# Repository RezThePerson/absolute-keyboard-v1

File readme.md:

# Absolute Keyboard v1

|  |  |
| --------------------------------------------------------------------------------------------------------------- | ------------------------------------------------------------------------------------------------------------------ |
|  |                                        |
|                                     |                                        |

A simple keeb with

- 65% layout (68 keey)
- rp2040 chip (aka embeeded custom board)
- neopixle for each switch
- hotspawp support
- minmilistic case
- qmk firmware

### Credits

guides:

- [Macondo's build a devboard](https://macondo.hackclub.com/docs/build-a-devboard)
- [Hackpad](https://hackpad.hackclub.com/guide)
- [Hackpad Advance Guide](https://hackpad-v2-backup.pages.dev/advancedguide) (only on backup page as of building this project)

other keebs i took inspiration from:

- [teds-kb-100](https://github.com/DovydasTEDS/teds-kb-100)
- [keeb-v2](https://github.com/Anayjain1129/keeb-v2)
- [FluxKeeb](https://github.com/Flux3tor/FluxKeeb)

kicad tools:

- [Keyboard footprints placer](https://github.com/adamws/kicad-kbplacer) plugin
- [MX_V2](https://github.com/ai03-2725/MX_V2) lib
- [marbast](https://github.com/ebastler/marbastlib) lib

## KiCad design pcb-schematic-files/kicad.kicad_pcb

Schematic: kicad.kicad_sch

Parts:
C1, C2, C3, C4, C5, C6, C7, C8, C10, C11, C17: 0.1uF; C_0402_1005Metric; LCSC C1525
C9, C12: 1uF; C_0402_1005Metric; LCSC C52923
C13, C14: 10uF; C_0603_1608Metric; LCSC 0603
C15, C16: 33pF; C_0402_1005Metric; LCSC C1562
C18: 100pF; C_0402_1005Metric; LCSC C1546
D1, D2, D3, D4, D5, D6, D7, D8, D9, D10, D11, D12, D13, D14, D15, D16, D17, D18, D19, D20, D21, D22, D23, D24, D25, D26, D27, D28, D29, D30, D31, D32, D33, D34, D35, D36, D37, D38, D39, D40, D41, D42, D43, D44, D45, D46, D47, D48, D49, D50, D51, D52, D53, D54, D55, D56, D57, D58, D59, D60, D61, D62, D63, D64, D65, D66, D67, D68: D; D_DO-35_SOD27_P7.62mm_Horizontal; LCSC 1N4148
J1: USB_C_Receptacle_USB2.0_14P; USB_C_Receptacle_HRO_TYPE-C-31-M-12; LCSC C165948
LED1, LED2, LED3, LED4, LED5, LED6, LED7, LED8, LED9, LED10, LED11, LED12, LED13, LED14, LED15, LED16, LED17, LED18, LED19, LED20, LED21, LED22, LED23, LED24, LED25, LED26, LED27, LED28, LED29, LED30, LED31, LED32, LED33, LED34, LED35, LED36, LED37, LED38, LED39, LED40, LED41, LED42, LED43, LED44, LED45, LED46, LED47, LED48, LED49, LED50, LED51, LED52, LED53, LED54, LED55, LED56, LED57, LED58, LED59, LED60, LED61, LED62, LED63, LED64, LED65, LED66, LED67, LED68: SK6812MINI-E; LED_6028R; LCSC C5149201
R1, R2: 5.1K; R_0402_1005Metric; LCSC C25905
R3, R4: 27; R_0402_1005Metric; LCSC C25100
R5, R6: 1K; R_0402_1005Metric; LCSC C11702
R7: 10K; R_0402_1005Metric; LCSC C25744
SW0: SW_Push; SW_Push_SPST_NO_Alps_SKRK; LCSC C115357
SW1, SW2, SW3, SW4, SW5, SW6, SW7, SW8, SW9, SW10, SW11, SW12, SW13, SW14, SW15, SW16, SW17, SW18, SW19, SW20, SW21, SW22, SW23, SW24, SW25, SW26, SW27, SW28, SW29, SW30, SW31, SW32, SW33, SW34, SW35, SW36, SW37, SW38, SW39, SW40, SW41, SW42, SW43, SW44, SW45, SW46, SW47, SW48, SW49, SW50, SW51, SW52, SW53, SW54, SW55, SW56, SW57, SW58, SW59, SW60, SW61, SW62, SW63, SW64, SW65, SW66, SW67, SW68: SW_Push; SW_MX_HS_CPG151101S11_1u; LCSC C49352235
U1: RP2040; QFN-56-1EP_7x7mm_P0.4mm_EP3.2x3.2mm; LCSC C2040
U2: NCP1117-3.3_SOT223; SOT-223-3_TabPin2; LCSC C6186
U3: W25Q128JVS; SOIC-8_5.3x5.3mm_P1.27mm; LCSC C97521
Y1: 12 MHz; Crystal_SMD_3225-4Pin_3.2x2.5mm; LCSC C9002

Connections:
+1V1: C10.1, C11.1, C12.1, U1.43 (ADC_AVDD), U1.48 (USB_VDD)
+3V3: C1.1, C2.1, C3.1, C4.1, C5.1, C6.1, C7.1, C8.1, C9.1, C14.1, C17.1, R7.2, U1.1 (IOVDD), U1.10 (IOVDD), U1.22 (IOVDD), U1.23 (DVDD), U1.33 (IOVDD), U1.42 (IOVDD), U1.44 (VREG_VIN), U1.45 (VREG_VOUT), U1.49 (IOVDD), U1.50 (DVDD), U2.2 (VO), U3.8 (VCC)
+5V: C13.1, C18.1, J1.A4 (VBUS), J1.A9 (VBUS), J1.B4 (VBUS), J1.B9 (VBUS), LED1.1 (VDD), LED2.1 (VDD), LED3.1 (VDD), LED4.1 (VDD), LED5.1 (VDD), LED6.1 (VDD), LED7.1 (VDD), LED8.1 (VDD), LED9.1 (VDD), LED10.1 (VDD), LED11.1 (VDD), LED12.1 (VDD), LED13.1 (VDD), LED14.1 (VDD), LED15.1 (VDD), LED16.1 (VDD), LED17.1 (VDD), LED18.1 (VDD), LED19.1 (VDD), LED20.1 (VDD), LED21.1 (VDD), LED22.1 (VDD), LED23.1 (VDD), LED24.1 (VDD), LED25.1 (VDD), LED26.1 (VDD), LED27.1 (VDD), LED28.1 (VDD), LED29.1 (VDD), LED30.1 (VDD), LED31.1 (VDD), LED32.1 (VDD), LED33.1 (VDD), LED34.1 (VDD), LED35.1 (VDD), LED36.1 (VDD), LED37.1 (VDD), LED38.1 (VDD), LED39.1 (VDD), LED40.1 (VDD), LED41.1 (VDD), LED42.1 (VDD), LED43.1 (VDD), LED44.1 (VDD), LED45.1 (VDD), LED46.1 (VDD), LED47.1 (VDD), LED48.1 (VDD), LED49.1 (VDD), LED50.1 (VDD), LED51.1 (VDD), LED52.1 (VDD), LED53.1 (VDD), LED54.1 (VDD), LED55.1 (VDD), LED56.1 (VDD), LED57.1 (VDD), LED58.1 (VDD), LED59.1 (VDD), LED60.1 (VDD), LED61.1 (VDD), LED62.1 (VDD), LED63.1 (VDD), LED64.1 (VDD), LED65.1 (VDD), LED66.1 (VDD), LED67.1 (VDD), LED68.1 (VDD), U2.3 (VI)
COL_1: SW1.1, SW16.1, SW31.1, SW45.1, SW59.1, U1.29 (GPIO18)
COL_2: SW2.1, SW17.1, SW32.1, SW46.1, SW60.1, U1.30 (GPIO19)
COL_3: SW3.1, SW18.1, SW33.1, SW47.1, SW61.1, U1.31 (GPIO20)
COL_4: SW4.1, SW19.1, SW34.1, SW48.1, SW62.1, U1.32 (GPIO21)
COL_5: SW5.1, SW20.1, SW35.1, SW49.1, U1.34 (GPIO22)
COL_6: SW6.1, SW21.1, SW36.1, SW50.1, U1.35 (GPIO23)
COL_7: SW7.1, SW22.1, SW37.1, SW51.1, U1.36 (GPIO24)
COL_8: SW8.1, SW23.1, SW38.1, SW52.1, U1.37 (GPIO25)
COL_9: SW9.1, SW24.1, SW39.1, SW53.1, SW63.1, U1.2 (GPIO0)
COL_10: SW10.1, SW25.1, SW40.1, SW54.1, SW64.1, U1.3 (GPIO1)
COL_11: SW11.1, SW26.1, SW41.1, SW55.1, SW65.1, U1.4 (GPIO2)
COL_12: SW12.1, SW27.1, SW42.1, SW56.1, SW66.1, U1.5 (GPIO3)
COL_13: SW13.1, SW28.1, SW43.1, SW57.1, SW67.1, U1.6 (GPIO4)
COL_14: SW14.1, SW29.1, SW44.1, SW58.1, SW68.1, U1.7 (GPIO5)
COL_15: SW15.1, SW30.1, U1.8 (GPIO6)
GND: C1.2, C2.2, C3.2, C4.2, C5.2, C6.2, C7.2, C8.2, C9.2, C10.2, C11.2, C12.2, C13.2, C14.2, C15.1, C16.1, C17.2, C18.2, J1.A1 (GND), J1.A12 (GND), J1.B1 (GND), J1.B12 (GND), J1.S1 (SHIELD), LED1.4 (VSS), LED2.4 (VSS), LED3.4 (VSS), LED4.4 (VSS), LED5.4 (VSS), LED6.4 (VSS), LED7.4 (VSS), LED8.4 (VSS), LED9.4 (VSS), LED10.4 (VSS), LED11.4 (VSS), LED12.4 (VSS), LED13.4 (VSS), LED14.4 (VSS), LED15.4 (VSS), LED16.4 (VSS), LED17.4 (VSS), LED18.4 (VSS), LED19.4 (VSS), LED20.4 (VSS), LED21.4 (VSS), LED22.4 (VSS), LED23.4 (VSS), LED24.4 (VSS), LED25.4 (VSS), LED26.4 (VSS), LED27.4 (VSS), LED28.4 (VSS), LED29.4 (VSS), LED30.4 (VSS), LED31.4 (VSS), LED32.4 (VSS), LED33.4 (VSS), LED34.4 (VSS), LED35.4 (VSS), LED36.4 (VSS), LED37.4 (VSS), LED38.4 (VSS), LED39.4 (VSS), LED40.4 (VSS), LED41.4 (VSS), LED42.4 (VSS), LED43.4 (VSS), LED44.4 (VSS), LED45.4 (VSS), LED46.4 (VSS), LED47.4 (VSS), LED48.4 (VSS), LED49.4 (VSS), LED50.4 (VSS), LED51.4 (VSS), LED52.4 (VSS), LED53.4 (VSS), LED54.4 (VSS), LED55.4 (VSS), LED56.4 (VSS), LED57.4 (VSS), LED58.4 (VSS), LED59.4 (VSS), LED60.4 (VSS), LED61.4 (VSS), LED62.4 (VSS), LED63.4 (VSS), LED64.4 (VSS), LED65.4 (VSS), LED66.4 (VSS), LED67.4 (VSS), LED68.4 (VSS), R1.2, R2.2, SW0.2, U1.57 (GND), U2.1 (GND), U3.4 (GND), Y1.2 (G), Y1.4 (G)
NEOPIXELS_1: LED1.3 (DIN), U1.11 (GPIO8)
NEOPIXELS_2: LED15.2 (DOUT), LED16.3 (DIN)
NEOPIXELS_3: LED30.2 (DOUT), LED31.3 (DIN)
NEOPIXELS_4: LED44.2 (DOUT), LED45.3 (DIN)
NEOPIXELS_5: LED58.2 (DOUT), LED59.3 (DIN)
unnamed: C16.2, R5.1, Y1.1
unnamed: D1.2 (A), SW1.2
unnamed: D2.2 (A), SW2.2
unnamed: D3.2 (A), SW3.2
unnamed: D4.2 (A), SW4.2
unnamed: D5.2 (A), SW5.2
unnamed: D6.2 (A), SW6.2
unnamed: D7.2 (A), SW7.2
unnamed: D8.2 (A), SW8.2
unnamed: D9.2 (A), SW9.2
unnamed: D10.2 (A), SW10.2
unnamed: D11.2 (A), SW11.2
unnamed: D12.2 (A), SW12.2
unnamed: D13.2 (A), SW13.2
unnamed: D14.2 (A), SW14.2
unnamed: D15.2 (A), SW15.2
unnamed: D16.2 (A), SW16.2
unnamed: D17.2 (A), SW17.2
unnamed: D18.2 (A), SW18.2
unnamed: D19.2 (A), SW19.2
unnamed: D20.2 (A), SW20.2
unnamed: D21.2 (A), SW21.2
unnamed: D22.2 (A), SW22.2
unnamed: D23.2 (A), SW23.2
unnamed: D24.2 (A), SW24.2
unnamed: D25.2 (A), SW25.2
unnamed: D26.2 (A), SW26.2
unnamed: D27.2 (A), SW27.2
unnamed: D28.2 (A), SW28.2
unnamed: D29.2 (A), SW29.2
unnamed: D30.2 (A), SW30.2
unnamed: D31.2 (A), SW31.2
unnamed: D32.2 (A), SW32.2
unnamed: D33.2 (A), SW33.2
unnamed: D34.2 (A), SW34.2
unnamed: D35.2 (A), SW35.2
unnamed: D36.2 (A), SW36.2
unnamed: D37.2 (A), SW37.2
unnamed: D38.2 (A), SW38.2
unnamed: D39.2 (A), SW39.2
unnamed: D40.2 (A), SW40.2
unnamed: D41.2 (A), SW41.2
unnamed: D42.2 (A), SW42.2
unnamed: D43.2 (A), SW43.2
unnamed: D44.2 (A), SW44.2
unnamed: D45.2 (A), SW45.2
unnamed: D46.2 (A), SW46.2
unnamed: D47.2 (A), SW47.2
unnamed: D48.2 (A), SW48.2
unnamed: D49.2 (A), SW49.2
unnamed: D50.2 (A), SW50.2
unnamed: D51.2 (A), SW51.2
unnamed: D52.2 (A), SW52.2
unnamed: D53.2 (A), SW53.2
unnamed: D54.2 (A), SW54.2
unnamed: D55.2 (A), SW55.2
unnamed: D56.2 (A), SW56.2
unnamed: D57.2 (A), SW57.2
unnamed: D58.2 (A), SW58.2
unnamed: D59.2 (A), SW59.2
unnamed: D60.2 (A), SW60.2
unnamed: D61.2 (A), SW61.2
unnamed: D62.2 (A), SW62.2
unnamed: D63.2 (A), SW63.2
unnamed: D64.2 (A), SW64.2
unnamed: D65.2 (A), SW65.2
unnamed: D66.2 (A), SW66.2
unnamed: D67.2 (A), SW67.2
unnamed: D68.2 (A), SW68.2
unnamed: J1.A5 (CC1), R1.1
unnamed: J1.B5 (CC2), R2.1
unnamed: LED1.2 (DOUT), LED2.3 (DIN)
unnamed: LED2.2 (DOUT), LED3.3 (DIN)
unnamed: LED3.2 (DOUT), LED4.3 (DIN)
unnamed: LED4.2 (DOUT), LED5.3 (DIN)
unnamed: LED5.2 (DOUT), LED6.3 (DIN)
unnamed: LED6.2 (DOUT), LED7.3 (DIN)
unnamed: LED7.2 (DOUT), LED8.3 (DIN)
unnamed: LED8.2 (DOUT), LED9.3 (DIN)
unnamed: LED9.2 (DOUT), LED10.3 (DIN)
unnamed: LED10.2 (DOUT), LED11.3 (DIN)
unnamed: LED11.2 (DOUT), LED12.3 (DIN)
unnamed: LED12.2 (DOUT), LED13.3 (DIN)
unnamed: LED13.2 (DOUT), LED14.3 (DIN)
unnamed: LED14.2 (DOUT), LED15.3 (DIN)
unnamed: LED16.2 (DOUT), LED17.3 (DIN)
unnamed: LED17.2 (DOUT), LED18.3 (DIN)
unnamed: LED18.2 (DOUT), LED19.3 (DIN)
unnamed: LED19.2 (DOUT), LED20.3 (DIN)
unnamed: LED20.2 (DOUT), LED21.3 (DIN)
unnamed: LED21.2 (DOUT), LED22.3 (DIN)
unnamed: LED22.2 (DOUT), LED23.3 (DIN)
unnamed: LED23.2 (DOUT), LED24.3 (DIN)
unnamed: LED24.2 (DOUT), LED25.3 (DIN)
unnamed: LED25.2 (DOUT), LED26.3 (DIN)
unnamed: LED26.2 (DOUT), LED27.3 (DIN)
unnamed: LED27.2 (DOUT), LED28.3 (DIN)
unnamed: LED28.2 (DOUT), LED29.3 (DIN)
unnamed: LED29.2 (DOUT), LED30.3 (DIN)
unnamed: LED31.2 (DOUT), LED32.3 (DIN)
unnamed: LED32.2 (DOUT), LED33.3 (DIN)
unnamed: LED33.2 (DOUT), LED34.3 (DIN)
unnamed: LED34.2 (DOUT), LED35.3 (DIN)
unnamed: LED35.2 (DOUT), LED36.3 (DIN)
unnamed: LED36.2 (DOUT), LED37.3 (DIN)
unnamed: LED37.2 (DOUT), LED38.3 (DIN)
unnamed: LED38.2 (DOUT), LED39.3 (DIN)
unnamed: LED39.2 (DOUT), LED40.3 (DIN)
unnamed: LED40.2 (DOUT), LED41.3 (DIN)
unnamed: LED41.2 (DOUT), LED42.3 (DIN)
unnamed: LED42.2 (DOUT), LED43.3 (DIN)
unnamed: LED43.2 (DOUT), LED44.3 (DIN)
unnamed: LED45.2 (DOUT), LED46.3 (DIN)
unnamed: LED46.2 (DOUT), LED47.3 (DIN)
unnamed: LED47.2 (DOUT), LED48.3 (DIN)
unnamed: LED48.2 (DOUT), LED49.3 (DIN)
unnamed: LED49.2 (DOUT), LED50.3 (DIN)
unnamed: LED50.2 (DOUT), LED51.3 (DIN)
unnamed: LED51.2 (DOUT), LED52.3 (DIN)
unnamed: LED52.2 (DOUT), LED53.3 (DIN)
unnamed: LED53.2 (DOUT), LED54.3 (DIN)
unnamed: LED54.2 (DOUT), LED55.3 (DIN)
unnamed: LED55.2 (DOUT), LED56.3 (DIN)
unnamed: LED56.2 (DOUT), LED57.3 (DIN)
unnamed: LED57.2 (DOUT), LED58.3 (DIN)
unnamed: LED59.2 (DOUT), LED60.3 (DIN)
unnamed: LED60.2 (DOUT), LED61.3 (DIN)
unnamed: LED61.2 (DOUT), LED62.3 (DIN)
unnamed: LED62.2 (DOUT), LED63.3 (DIN)
unnamed: LED63.2 (DOUT), LED64.3 (DIN)
unnamed: LED64.2 (DOUT), LED65.3 (DIN)
unnamed: LED65.2 (DOUT), LED66.3 (DIN)
unnamed: LED66.2 (DOUT), LED67.3 (DIN)
unnamed: LED67.2 (DOUT), LED68.3 (DIN)
unnamed: R6.1, SW0.1
unnamed: R3.2, U1.46 (USB_DM)
unnamed: R4.2, U1.47 (USB_DP)
QSPI_SCLK: U1.52 (QSPI_SCLK), U3.6 (CLK)
QSPI_SD0: U1.53 (QSPI_SD0), U3.5 (DI/IO_{0})
QSPI_SD1: U1.55 (QSPI_SD1), U3.2 (DO/IO_{1})
QSPI_SD2: U1.54 (QSPI_SD2), U3.3 (~WP/IO_{2})
QSPI_SD3: U1.51 (QSPI_SD3), U3.7 (~HOLD/~RESET/IO_{3})
QSPI_SS: R6.2, R7.1, U1.56 (~QSPI_SS), U3.1 (~CS)
ROW_1: D1.1 (K), D2.1 (K), D3.1 (K), D4.1 (K), D5.1 (K), D6.1 (K), D7.1 (K), D8.1 (K), D9.1 (K), D10.1 (K), D11.1 (K), D12.1 (K), D13.1 (K), D14.1 (K), D15.1 (K), U1.18 (GPIO15)
ROW_2: D16.1 (K), D17.1 (K), D18.1 (K), D19.1 (K), D20.1 (K), D21.1 (K), D22.1 (K), D23.1 (K), D24.1 (K), D25.1 (K), D26.1 (K), D27.1 (K), D28.1 (K), D29.1 (K), D30.1 (K), U1.17 (GPIO14)
ROW_3: D31.1 (K), D32.1 (K), D33.1 (K), D34.1 (K), D35.1 (K), D36.1 (K), D37.1 (K), D38.1 (K), D39.1 (K), D40.1 (K), D41.1 (K), D42.1 (K), D43.1 (K), D44.1 (K), U1.16 (GPIO13)
ROW_4: D45.1 (K), D46.1 (K), D47.1 (K), D48.1 (K), D49.1 (K), D50.1 (K), D51.1 (K), D52.1 (K), D53.1 (K), D54.1 (K), D55.1 (K), D56.1 (K), D57.1 (K), D58.1 (K), U1.15 (GPIO12)
ROW_5: D59.1 (K), D60.1 (K), D61.1 (K), D62.1 (K), D63.1 (K), D64.1 (K), D65.1 (K), D66.1 (K), D67.1 (K), D68.1 (K), U1.14 (GPIO11)
USB_D+: J1.A6 (D+), J1.B6 (D+), R3.1
USB_D-: J1.A7 (D-), J1.B7 (D-), R4.1
XIN: C15.2, U1.20 (XIN), Y1.3
XOUT: R5.2, U1.21 (XOUT)

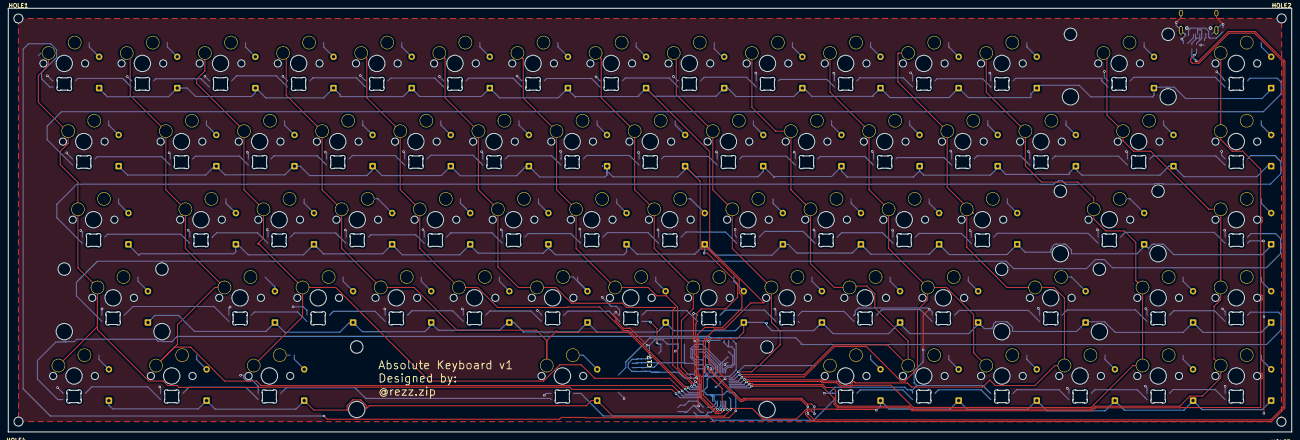
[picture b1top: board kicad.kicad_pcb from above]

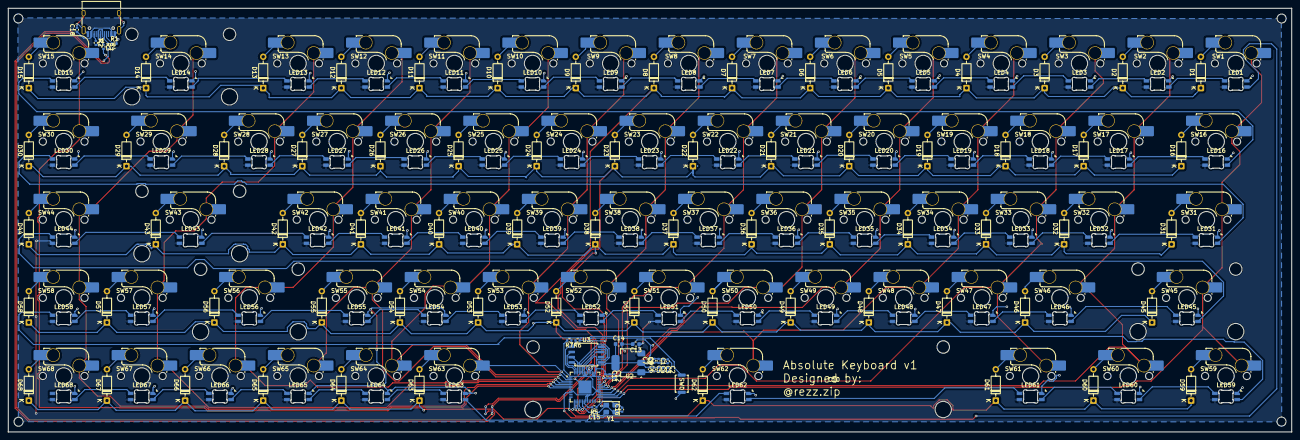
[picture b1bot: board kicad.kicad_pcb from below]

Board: 2 copper layers, 312.9 x 103.3 mm, 243 parts (235 on the bottom side), 176 nets.

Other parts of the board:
HOLE1, HOLE2, HOLE3, HOLE4: MountingHole_2.2mm_M2
MOUNT1, MOUNT3, MOUNT4, MOUNT5: STAB_MX_2u

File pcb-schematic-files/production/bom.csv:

Designator,Footprint,Quantity,Value,LCSC Part #
"C1, C10, C11, C17, C2, C3, C4, C5, C6, C7, C8",0402,11,0.1uF,C1525
"C12, C9",0402,2,1uF,C52923
"C13, C14",0603,2,10uF,0603
"C15, C16",0402,2,33pF,C1562
C18,0402,1,100pF,C1546
"D1, D10, D11, D12, D13, D14, D15, D16, D17, D18, D19, D2, D20, D21, D22, D23, D24, D25, D26, D27, D28, D29, D3, D30, D31, D32, D33, D34, D35, D36, D37, D38, D39, D4, D40, D41, D42, D43, D44, D45, D46, D47, D48, D49, D5, D50, D51, D52, D53, D54, D55, D56, D57, D58, D59, D6, D60, D61, D62, D63, D64, D65, D66, D67, D68, D7, D8, D9",D_DO-35_SOD27_P7.62mm_Horizontal,68,D,1N4148
J1,USB_C_Receptacle_HRO_TYPE-C-31-M-12,1,USB_C_Receptacle_USB2.0_14P,C165948
"LED1, LED10, LED11, LED12, LED13, LED14, LED15, LED16, LED17, LED18, LED19, LED2, LED20, LED21, LED22, LED23, LED24, LED25, LED26, LED27, LED28, LED29, LED3, LED30, LED31, LED32, LED33, LED34, LED35, LED36, LED37, LED38, LED39, LED4, LED40, LED41, LED42, LED43, LED44, LED45, LED46, LED47, LED48, LED49, LED5, LED50, LED51, LED52, LED53, LED54, LED55, LED56, LED57, LED58, LED59, LED6, LED60, LED61, LED62, LED63, LED64, LED65, LED66, LED67, LED68, LED7, LED8, LED9",LED_6028R,68,SK6812MINI-E,C5149201
"R1, R2",0402,2,5.1K,C25905
"R3, R4",0402,2,27,C25100
"R5, R6",0402,2,1K,C11702
R7,0402,1,10K,C25744
SW0,SW_Push_SPST_NO_Alps_SKRK,1,SW_Push,C115357
"SW1, SW10, SW11, SW12, SW13, SW14, SW15, SW16, SW17, SW18, SW19, SW2, SW20, SW21, SW22, SW23, SW24, SW25, SW26, SW27, SW28, SW29, SW3, SW30, SW31, SW32, SW33, SW34, SW35, SW36, SW37, SW38, SW39, SW4, SW40, SW41, SW42, SW43, SW44, SW45, SW46, SW47, SW48, SW49, SW5, SW50, SW51, SW52, SW53, SW54, SW55, SW56, SW57, SW58, SW59, SW6, SW60, SW61, SW62, SW63, SW64, SW65, SW66, SW67, SW68, SW7, SW8, SW9",SW_MX_HS_CPG151101S11_1u,68,SW_Push,C49352235
U1,QFN-56-1EP_7x7mm_P0.4mm_EP3.2x3.2mm,1,RP2040,C2040
U2,SOT-223-3_TabPin2,1,NCP1117-3.3_SOT223,C6186
U3,SOIC-8_5.3x5.3mm_P1.27mm,1,W25Q128JVS,C97521
Y1,Crystal_SMD_3225-4Pin_3.2x2.5mm,1,12 MHz,C9002

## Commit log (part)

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2026-06-03 init
2026-06-03 sfdsd
2026-06-03 sfdfsf
2026-06-10 fsfds
2026-06-10 sadads
2026-06-10 fdsfds
2026-06-10 sfdd
2026-06-10 sdsdffds
2026-06-11 dfdfds
2026-06-11 sdfsd
2026-06-11 sfdsf
2026-06-11 dsadas
2026-06-12 sfdfdsfd
2026-06-15 ewrwre
2026-06-15 sdfdsf
2026-06-15 sfdfds
2026-06-16 fsdfsd
2026-06-16 fssf
2026-06-16 fsdfs
2026-06-17 fdsdsf
2026-06-17 dsfds
2026-06-17 dsffd
2026-06-24 fsdsfd
2026-06-24 gdgfd
2026-06-24 sfdsfd
2026-06-24 sfdsdf
